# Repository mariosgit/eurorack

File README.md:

# Changes by mariosgit..

in branch mb/402to603
* Marbles 402->603
* Paits 402->603

in branch master
* Stages, fixed LED resistor 15k -> 150ohm
* Grids changed plug footprint

# Mutable Instruments' Eurorack Modules.

* [Blades](http://mutable-instruments.net/modules/blades): Dual multimode filter.
* [Blinds](http://mutable-instruments.net/modules/blinds): Quad VC-polarizer.
* [Braids](http://mutable-instruments.net/modules/braids): Macro-oscillator.
* [Branches](http://mutable-instruments.net/modules/branches): Dual Bernoulli gate.
* [Clouds](http://mutable-instruments.net/modules/clouds): Texture synthesizer.
* [Ears](http://mutable-instruments.net/modules/ears): Contact microphone.
* [Edges](http://mutable-instruments.net/modules/edges): Quad chiptune digital oscillator.
* [Elements](http://mutable-instruments.net/modules/elements): Modal synthesizer.
* [Frames](http://mutable-instruments.net/modules/frames): Keyframer/mixer.
* [Grids](http://mutable-instruments.net/modules/grids): Topographic drum sequencer.
* [Kinks](http://mutable-instruments.net/modules/kinks): Utility module - rectifier, analog logic, S&H, noise.
* [Links](http://mutable-instruments.net/modules/links): Utility module - buffer, mixer.
* [Marbles](http://mutable-instruments.net/modules/marbles): Random sampler.
* [Peaks](http://mutable-instruments.net/modules/peaks): Dual trigger converter.
* [Plaits](http://mutable-instruments.net/modules/plaits): Macro oscillator.
* [Rings](http://mutable-instruments.net/modules/rings): Resonator.
* [Ripples](http://mutable-instruments.net/modules/ripples): Liquid 2-pole BP, 2-pole LP and 4-pole LP filter.
* [Shades](http://mutable-instruments.net/modules/shades): Triple attenuverter.
* [Shelves](http://mutable-instruments.net/modules/shelves): EQ filter.
* [Stages](http://mutable-instruments.net/modules/stages): Segment generator.
* [Streams](http://mutable-instruments.net/modules/streams): Dual dynamics gate.
* [Tides](http://mutable-instruments.net/modules/tides): Tidal modulator.
* [Veils](http://mutable-instruments.net/modules/veils): Quad VCA.
* [Volts](http://mutable-instruments.net/modules/volts): +5V power module.
* [Warps](http://mutable-instruments.net/modules/warps): Meta-modulator.
* [Yarns](http://mutable-instruments.net/modules/yarns): MIDI interface.

License
=======

Code (AVR projects): GPL3.0.

Code (STM32F projects): MIT license.

Hardware: cc-by-sa-3.0

By: Emilie Gillet (emilie.o.gillet@gmail.com)

Guidelines for derivative works
===============================

**Mutable Instruments is a registered trademark.**

The name "Mutable Instruments" should not be used on any of the derivative works you create from these files.

We do not recommend you to keep the original name of the Mutable Instruments module for your derivative works.

For example, your 5U adaptation of Mutable Instruments Clouds can be called "Foobar Modular - Particle Generator".

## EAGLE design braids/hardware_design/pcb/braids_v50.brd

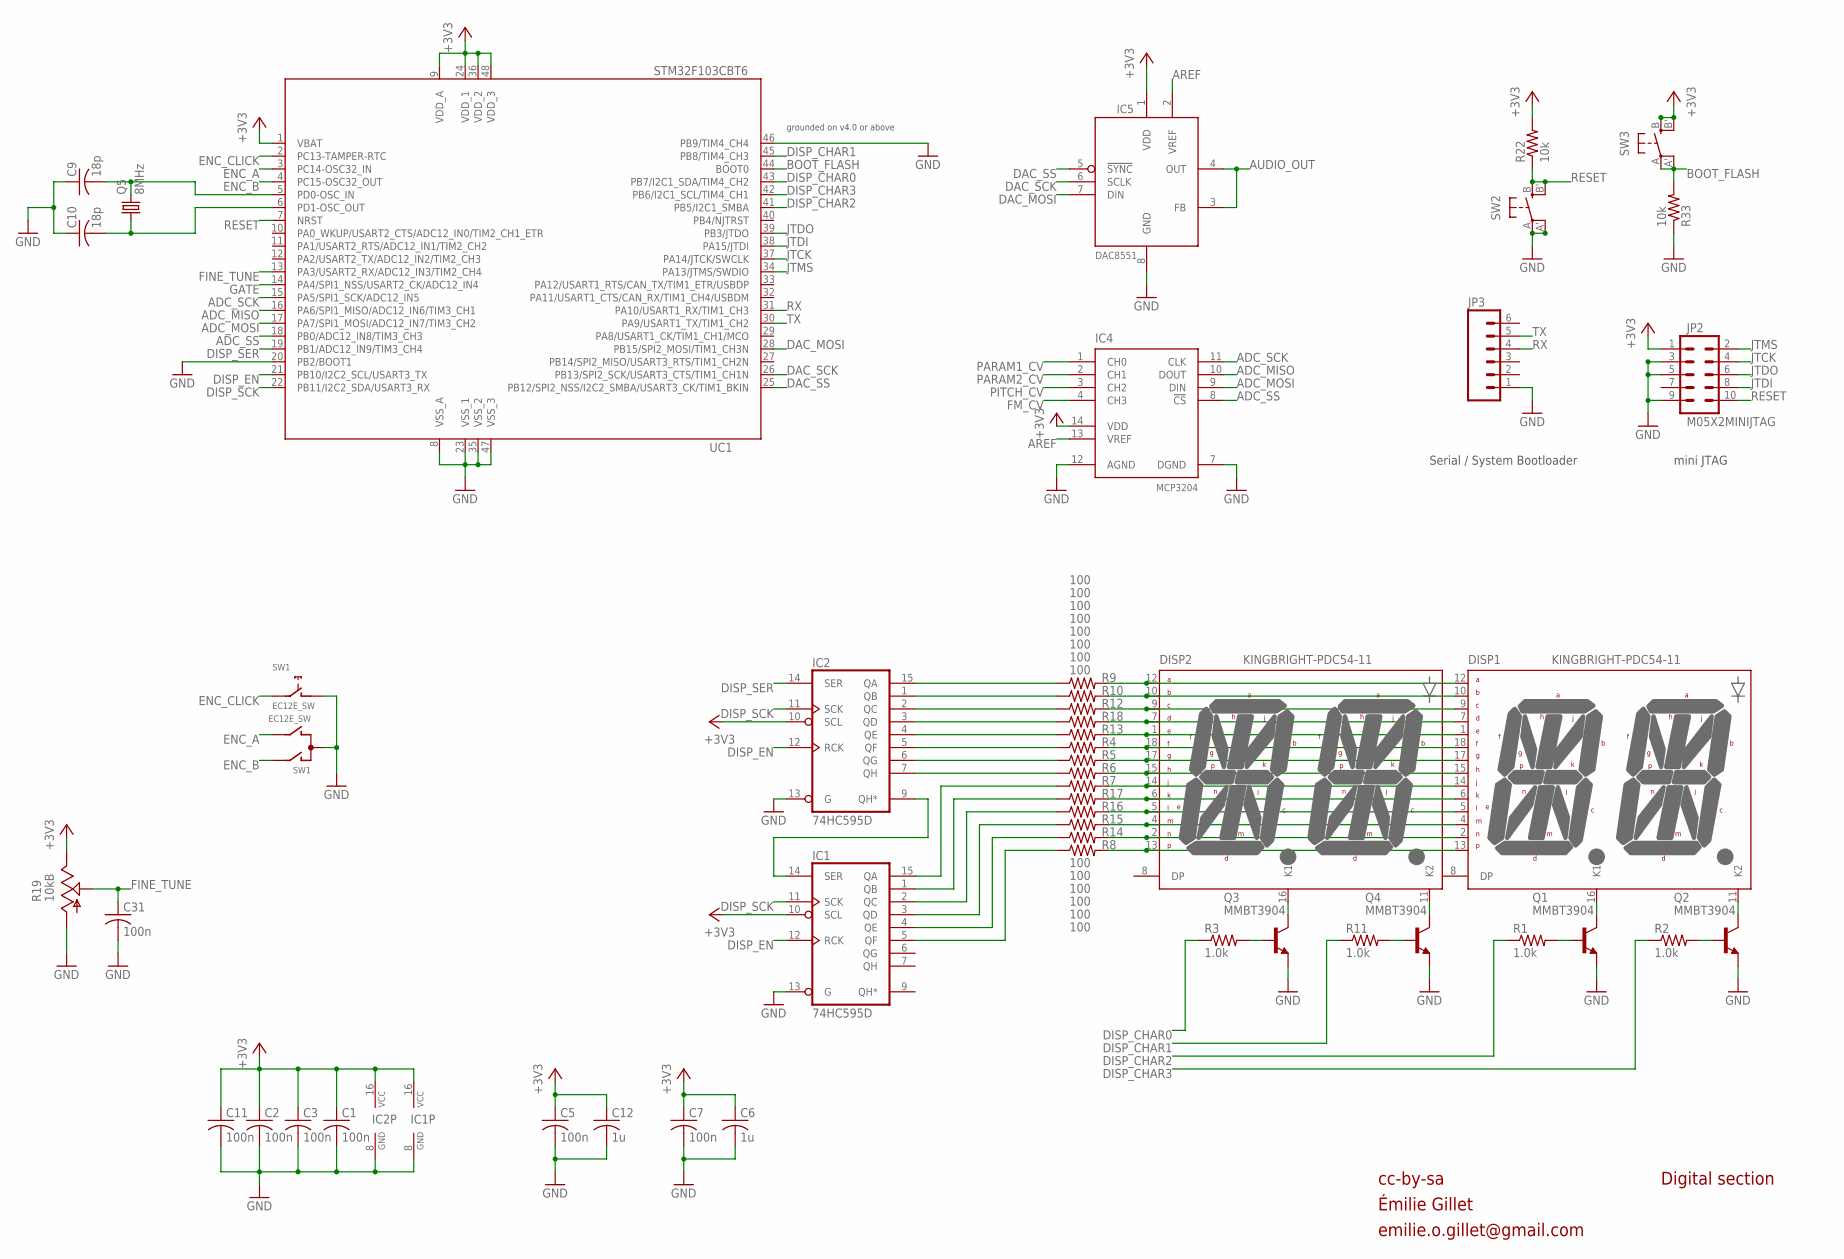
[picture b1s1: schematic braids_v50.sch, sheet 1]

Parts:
C1, C2, C3, C5, C7, C11, C31: 100n; C0603
C6, C12: 1u; C0603
C9, C10: 18p; C0603
DISP1, DISP2: KINGBRIGHT-PDC54-11; PDC54
IC1, IC2: 74HC595D; SO16
IC4: MCP3204; SO14
IC5: DAC8551; MSOP-8
JP2: M05X2MINIJTAG; 2X5-1.27
JP3: M06SIP; 1X06
Q1, Q2, Q3, Q4: MMBT3904; SOT23-BEC
Q5: 8MHz; HC49UP
R1, R2, R3, R11: 1.0k; R0603
R4, R5, R6, R7, R8, R9, R10, R12, R13, R14, R15, R16, R17, R18: 100; R0603
R19: 10kB; ALPS_POT_VERTICAL_PS
R22, R33: 10k; R0603
SW1: EC12E_SW; ALPS_EC12E_SW
SW2, SW3: EVQQ2; EVQ-Q2
UC1: STM32F103CBT6; LQFP48

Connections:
+3V3: C1.1, C2.1, C3.1, C5.1, C6.1, C7.1, C11.1, C12.1, IC1.10 (SCL), IC1.16 (VCC), IC2.10 (SCL), IC2.16 (VCC), IC4.14 (VDD), IC5.1 (VDD), JP2.1, R19.P$1 (E), R22.2, SW3.B (S), SW3.B' (S1), UC1.1 (VBAT), UC1.9 (VDD_A), UC1.24 (VDD_1), UC1.36 (VDD_2), UC1.48 (VDD_3); also elsewhere on the board
ADC_MISO: IC4.10 (DOUT), UC1.16 (PA6/SPI1_MISO/ADC12_IN6/TIM3_CH1)
ADC_MOSI: IC4.9 (DIN), UC1.17 (PA7/SPI1_MOSI/ADC12_IN7/TIM3_CH2)
ADC_SCK: IC4.11 (CLK), UC1.15 (PA5/SPI1_SCK/ADC12_IN5)
ADC_SS: IC4.8 (!CS), UC1.18 (PB0/ADC12_IN8/TIM3_CH3)
AREF: IC4.13 (VREF), IC5.2 (VREF); also elsewhere on the board
AUDIO_OUT: IC5.3 (FB), IC5.4 (OUT); also elsewhere on the board
BOOT_FLASH: R33.2, SW3.A, SW3.A' (P1), UC1.44 (BOOT0)
DAC_MOSI: IC5.7 (DIN), UC1.28 (PB15/SPI2_MOSI/TIM1_CH3N)
DAC_SCK: IC5.6 (SCLK), UC1.26 (PB13/SPI2_SCK/USART3_CTS/TIM1_CH1N)
DAC_SS: IC5.5 (!SYNC), UC1.25 (PB12/SPI2_NSS/I2C2_SMBA/USART3_CK/TIM1_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)
DISP_CHAR0: R3.1, UC1.43 (PB7/I2C1_SDA/TIM4_CH2)
DISP_CHAR1: R11.1, UC1.45 (PB8/TIM4_CH3)
DISP_CHAR2: R1.1, UC1.41 (PB5/I2C1_SMBA)
DISP_CHAR3: R2.1, UC1.42 (PB6/I2C1_SCL/TIM4_CH1)
DISP_EN: IC1.12 (RCK), IC2.12 (RCK), UC1.21 (PB10/I2C2_SCL/USART3_TX)
DISP_SCK: IC1.11 (SCK), IC2.11 (SCK), UC1.22 (PB11/I2C2_SDA/USART3_RX)
DISP_SER: IC2.14 (SER), UC1.19 (PB1/ADC12_IN9/TIM3_CH4)
ENC_A: SW1.B, UC1.3 (PC14-OSC32_IN)
ENC_B: SW1.A, UC1.4 (PC15-OSC32_OUT)
ENC_CLICK: SW1.E (2), UC1.2 (PC13-TAMPER-RTC)
FINE_TUNE: C31.1, R19.P$2 (S), UC1.13 (PA3/USART2_RX/ADC12_IN3/TIM2_CH4)
FM_CV: IC4.4 (CH3); also elsewhere on the board
GATE: UC1.14 (PA4/SPI1_NSS/USART2_CK/ADC12_IN4); also elsewhere on the board
GND: C1.2, C2.2, C3.2, C5.2, C6.2, C7.2, C9.1, C10.1, C11.2, C12.2, C31.2, IC1.8 (GND), IC1.13 (G), IC2.8 (GND), IC2.13 (G), IC4.7 (DGND), IC4.12 (AGND), IC5.8 (GND), JP2.3, JP2.5, JP2.9, JP3.1, Q1.E, Q2.E, Q3.E, Q4.E, R19.P$3 (A), R33.1, SW1.C, SW1.D (1), SW2.A, SW2.A' (P1), UC1.8 (VSS_A), UC1.20 (PB2/BOOT1), UC1.23 (VSS_1), UC1.35 (VSS_2), UC1.46 (PB9/TIM4_CH4), UC1.47 (VSS_3); also elsewhere on the board
JTCK: JP2.4, UC1.37 (PA14/JTCK/SWCLK)
JTDI: JP2.8, UC1.38 (PA15/JTDI)
JTDO: JP2.6, UC1.39 (PB3/JTDO)
JTMS: JP2.2, UC1.34 (PA13/JTMS/SWDIO)
unnamed: DISP2.16 (K1), Q3.C
unnamed: DISP2.11 (K2), Q4.C
unnamed: DISP1.16 (K1), Q1.C
unnamed: DISP1.11 (K2), Q2.C
unnamed: Q3.B, R3.2
unnamed: Q4.B, R11.2
unnamed: C9.2, Q5.2, UC1.5 (PD0-OSC_IN)
unnamed: C10.2, Q5.1, UC1.6 (PD1-OSC_OUT)
unnamed: Q1.B, R1.2
unnamed: Q2.B, R2.2
unnamed: DISP1.12 (A), DISP2.12 (A), R9.2
unnamed: DISP1.10 (B), DISP2.10 (B), R10.2
unnamed: DISP1.9 (C), DISP2.9 (C), R12.2
unnamed: DISP1.7 (D), DISP2.7 (D), R18.2
unnamed: DISP1.1 (E), DISP2.1 (E), R13.2
unnamed: DISP1.18 (F), DISP2.18 (F), R4.2
unnamed: DISP1.17 (G), DISP2.17 (G), R5.2
unnamed: DISP1.15 (H), DISP2.15 (H), R6.2
unnamed: DISP1.14 (J), DISP2.14 (J), R7.2
unnamed: DISP1.6 (K), DISP2.6 (K), R17.2
unnamed: DISP1.5 (L), DISP2.5 (L), R16.2
unnamed: DISP1.4 (M), DISP2.4 (M), R15.2
unnamed: DISP1.2 (N), DISP2.2 (N), R14.2
unnamed: DISP1.13, DISP2.13, R8.2
unnamed: IC2.7 (QH), R6.1
unnamed: IC1.14 (SER), IC2.9 (QH*)
unnamed: IC2.15 (QA), R9.1
unnamed: IC2.1 (QB), R10.1
unnamed: IC2.2 (QC), R12.1
unnamed: IC2.3 (QD), R18.1
unnamed: IC2.4 (QE), R13.1
unnamed: IC2.5 (QF), R4.1
unnamed: IC2.6 (QG), R5.1
unnamed: IC1.15 (QA), R7.1
unnamed: IC1.1 (QB), R17.1
unnamed: IC1.2 (QC), R16.1
unnamed: IC1.3 (QD), R15.1
unnamed: IC1.4 (QE), R14.1
unnamed: IC1.5 (QF), R8.1
PARAM1_CV: IC4.1 (CH0); also elsewhere on the board
PARAM2_CV: IC4.2 (CH1); also elsewhere on the board
PITCH_CV: IC4.3 (CH2); also elsewhere on the board
RESET: JP2.10, R22.1, SW2.B (S), SW2.B' (S1), UC1.7 (NRST)
RX: JP3.4, UC1.31 (PA10/USART1_RX/TIM1_CH3)
TX: JP3.5, UC1.30 (PA9/USART1_TX/TIM1_CH2)

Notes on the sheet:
cc-by-sa
Serial / System Bootloader
mini JTAG
Digital section
grounded on v4.0 or above
Émilie Gillet
emilie.o.gillet@gmail.com

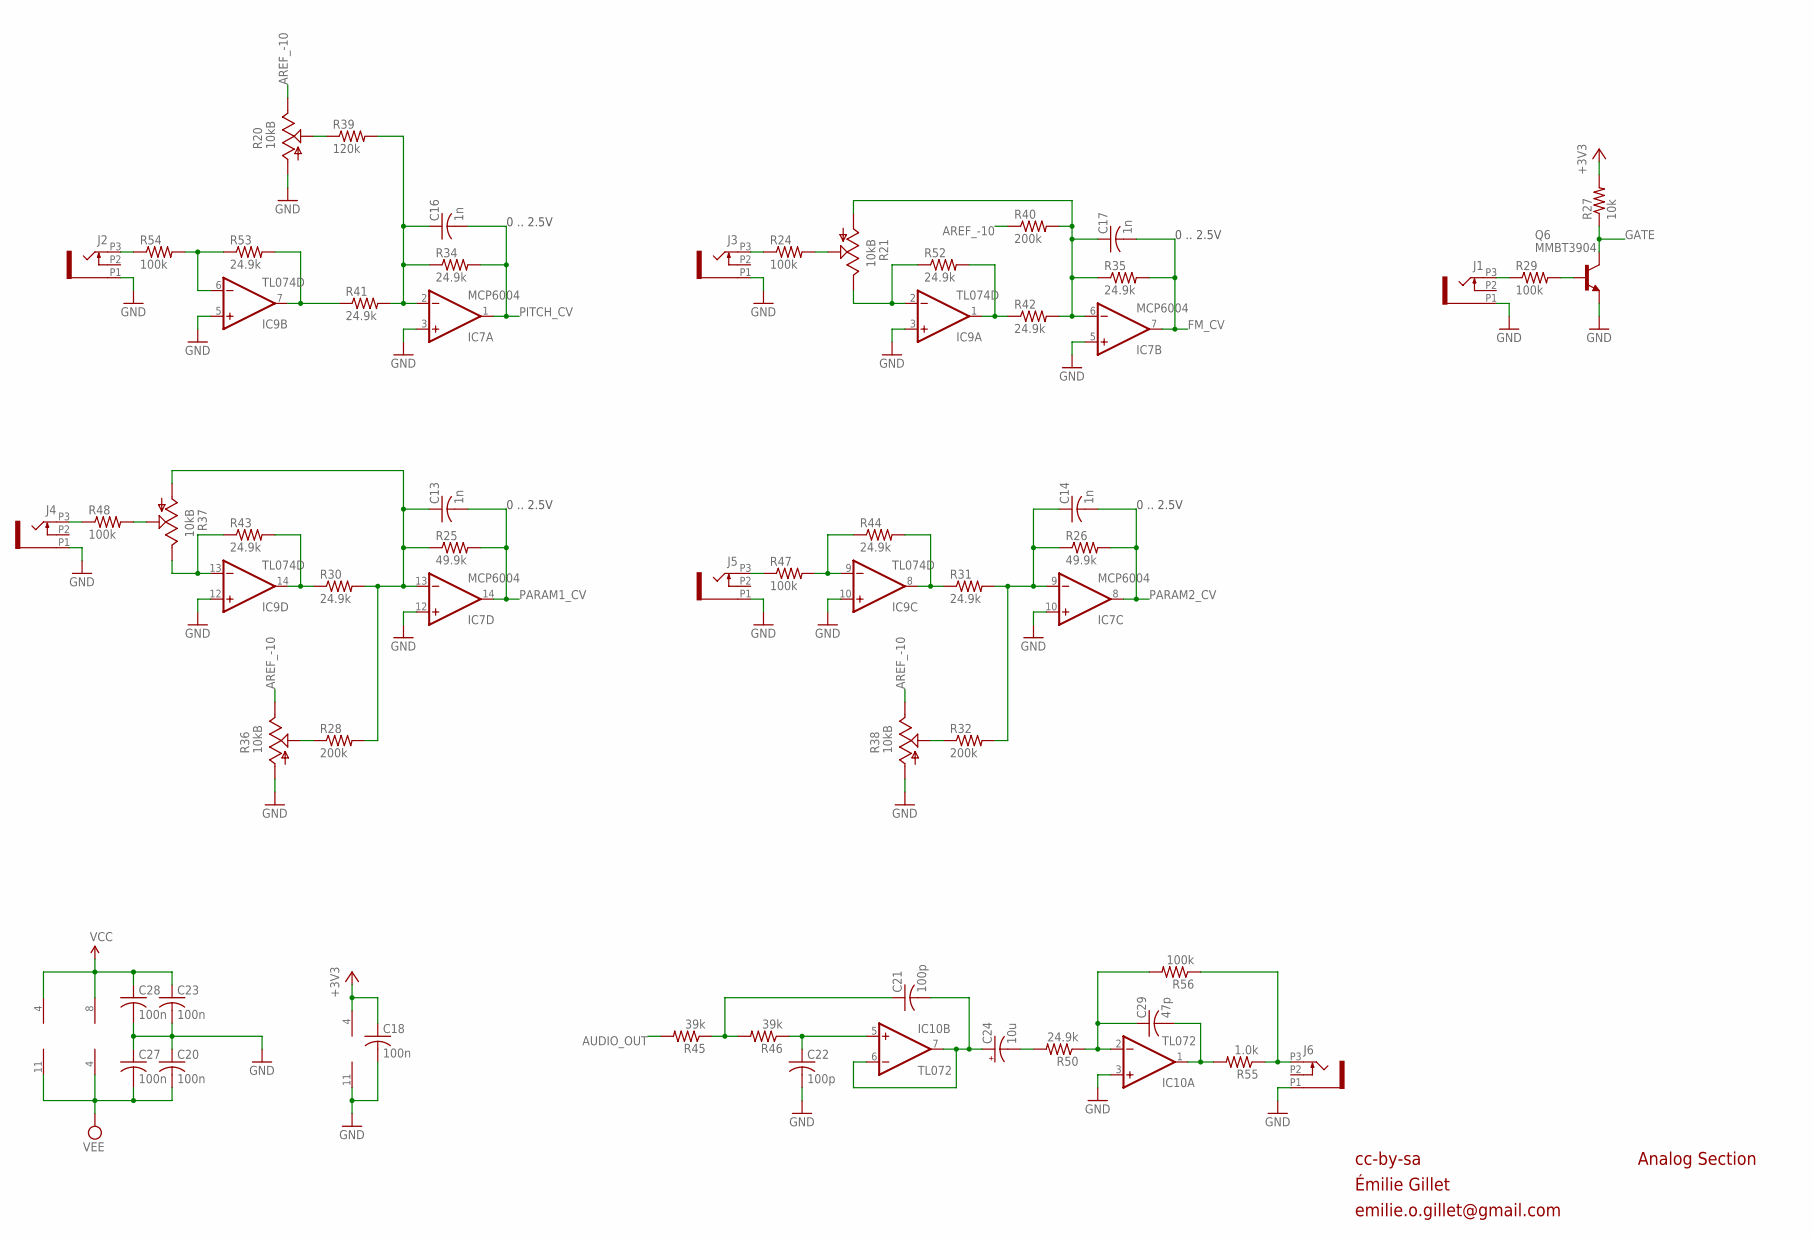
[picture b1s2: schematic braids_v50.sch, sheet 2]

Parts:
C13, C14, C16, C17: 1n; C0603
C18, C20, C23, C27, C28: 100n; C0603
C21, C22: 100p; C0603
C24: 10u; PANASONIC_B
C29: 47p; C0603
IC7: MCP6004; SO14
IC9: TL074D; SO14
IC10: TL072; SO08
J1, J2, J3, J4, J5, J6: PJ301_THONKICONN6; WQP_PJ_301M6
Q6: MMBT3904; SOT23-BEC
R20, R21, R36, R37, R38: 10kB; ALPS_POT_VERTICAL_PS
R24, R29, R47, R48, R54, R56: 100k; R0603
R25, R26: 49.9k; R0603
R27: 10k; R0603
R28, R32, R40: 200k; R0603
R30, R31, R34, R35, R41, R42, R43, R44, R50, R52, R53: 24.9k; R0603
R39: 120k; R0603
R45, R46: 39k; R0603
R55: 1.0k; R0603

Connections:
+3V3: C18.1, IC7.4 (V+), R27.2; also elsewhere on the board
AREF_-10: R20.P$1 (E), R36.P$1 (E), R38.P$1 (E), R40.1; also elsewhere on the board
AUDIO_OUT: R45.2; also elsewhere on the board
FM_CV: C17.2, IC7.7 (OUT), R35.2; also elsewhere on the board
GATE: Q6.C, R27.1; also elsewhere on the board
GND: C18.2, C20.1, C22.2, C23.2, C27.1, C28.2, IC7.3 (+IN), IC7.5 (+IN), IC7.10 (+IN), IC7.11 (V-), IC7.12 (+IN), IC9.3 (+IN), IC9.5 (+IN), IC9.10 (+IN), IC9.12 (+IN), IC10.3 (+IN), J1.P1 (1), J2.P1 (1), J3.P1 (1), J4.P1 (1), J5.P1 (1), J6.P1 (1), Q6.E, R20.P$3 (A), R36.P$3 (A), R38.P$3 (A); also elsewhere on the board
unnamed: IC9.7 (OUT), R41.1, R53.2
unnamed: R20.P$2 (S), R39.1
unnamed: J2.P3 (3), R54.1
unnamed: C16.1, IC7.2 (-IN), R34.1, R39.2, R41.2
unnamed: IC9.6 (-IN), R53.1, R54.2
unnamed: J3.P3 (3), R24.1
unnamed: J4.P3 (3), R48.1
unnamed: R21.P$2 (S), R24.2
unnamed: IC9.13 (-IN), R37.P$1 (E), R43.1
unnamed: IC9.14 (OUT), R30.1, R43.2
unnamed: IC9.2 (-IN), R21.P$1 (E), R52.1
unnamed: IC9.1 (OUT), R42.1, R52.2
unnamed: C17.1, IC7.6 (-IN), R21.P$3 (A), R35.1, R40.2, R42.2
unnamed: J1.P3 (3), R29.1
unnamed: IC9.8 (OUT), R31.1, R44.2
unnamed: C13.1, IC7.13 (-IN), R25.1, R28.2, R30.2, R37.P$3 (A)
unnamed: J5.P3 (3), R47.1
unnamed: R28.1, R36.P$2 (S)
unnamed: R37.P$2 (S), R48.2
unnamed: IC9.9 (-IN), R44.1, R47.2
unnamed: R32.1, R38.P$2 (S)
unnamed: Q6.B, R29.2
unnamed: C21.2, C24.+, IC10.6 (-IN), IC10.7 (OUT)
unnamed: C24.-, R50.2
unnamed: C22.1, IC10.5 (+IN), R46.1
unnamed: C14.1, IC7.9 (-IN), R26.1, R31.2, R32.2
unnamed: C21.1, R45.1, R46.2
unnamed: J6.P3 (3), R55.1, R56.1
unnamed: C29.2, IC10.1 (OUT), R55.2
unnamed: C29.1, IC10.2 (-IN), R50.1, R56.2
PARAM1_CV: C13.2, IC7.14 (OUT), R25.2; also elsewhere on the board
PARAM2_CV: C14.2, IC7.8 (OUT), R26.2; also elsewhere on the board
PITCH_CV: C16.2, IC7.1 (OUT), R34.2; also elsewhere on the board
VCC: C23.1, C28.1, IC9.4 (V+), IC10.8 (V+); also elsewhere on the board
VEE: C20.2, C27.2, IC9.11 (V-), IC10.4 (V-); also elsewhere on the board

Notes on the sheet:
cc-by-sa
Analog Section
0 .. 2.5V
Émilie Gillet
emilie.o.gillet@gmail.com

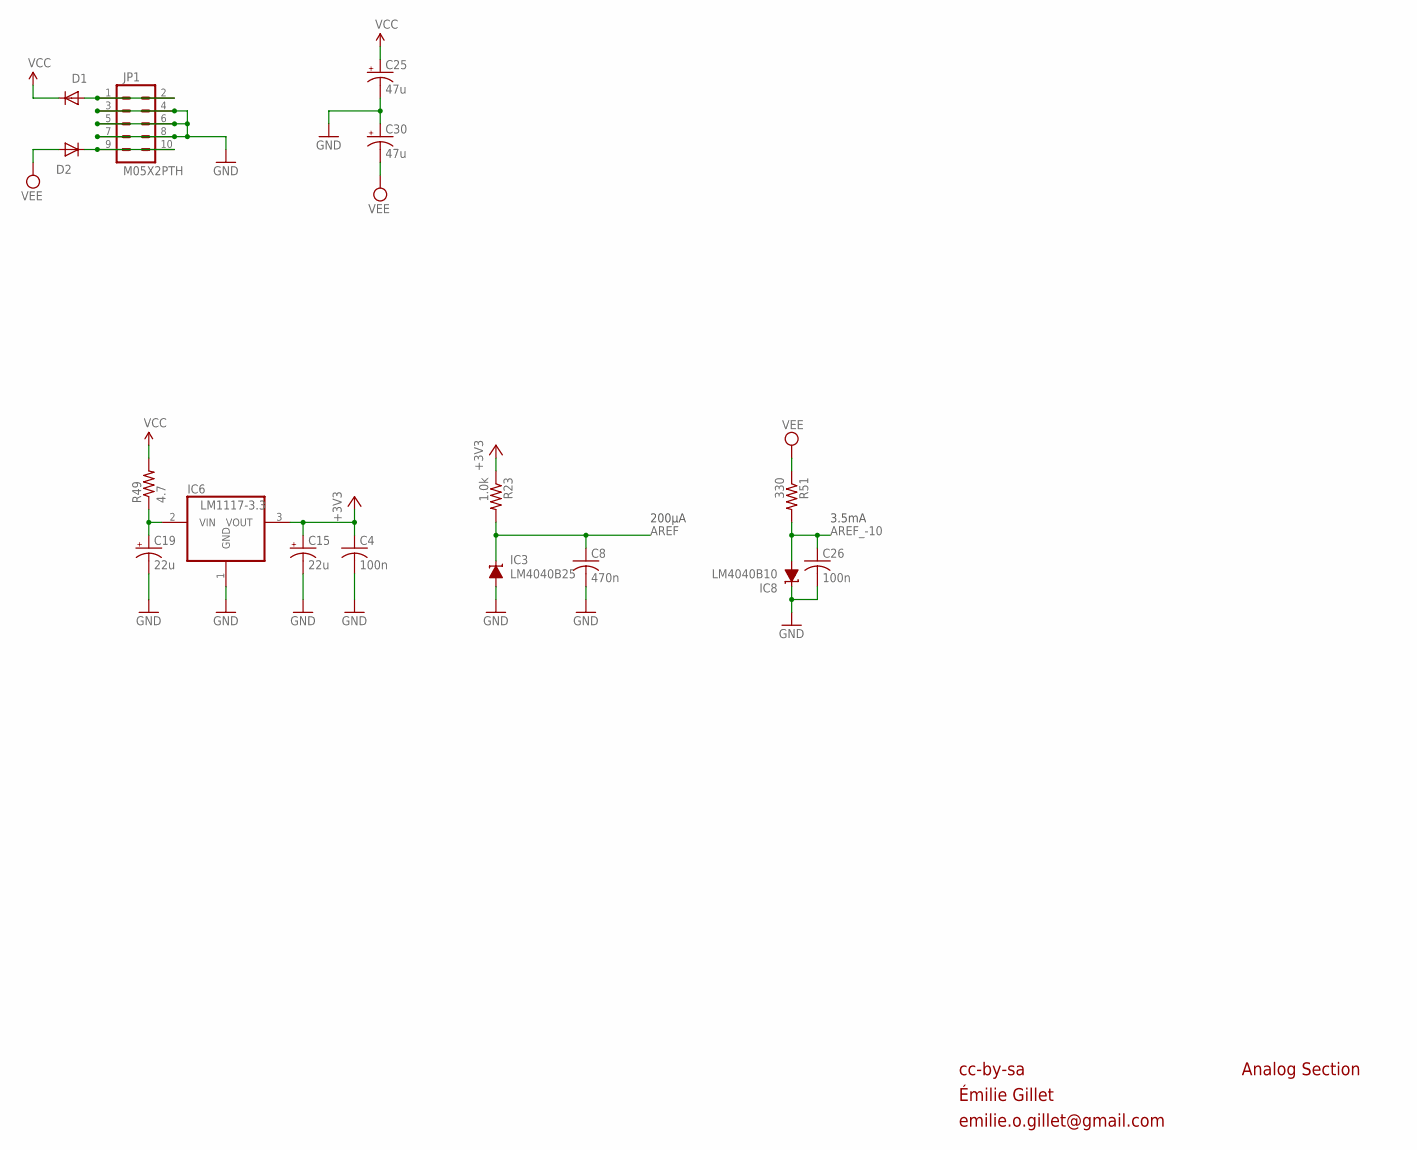
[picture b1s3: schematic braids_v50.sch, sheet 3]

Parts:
C4, C26: 100n; C0603
C8: 470n; C0603
C15, C19: 22u; PANASONIC_C
C25, C30: 47u; PANASONIC_D
D1, D2: 1N5819HW; SOD123
IC3: LM4040B25; DBZ_R-PDSO-G3
IC6: LM1117-3.3; TO252
IC8: LM4040B10; DBZ_R-PDSO-G3
JP1: M05X2PTH; AVR_ICSP
R23: 1.0k; R0603
R49: 4.7; R1206
R51: 330; R0603

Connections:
+3V3: C4.1, C15.+, IC6.3 (VOUT), R23.1; also elsewhere on the board
AREF: C8.1, IC3.1 (C), R23.2; also elsewhere on the board
AREF_-10: C26.1, IC8.2 (A), R51.2; also elsewhere on the board
GND: C4.2, C8.2, C15.-, C19.-, C25.-, C26.2, C30.+, IC3.2 (A), IC6.1 (GND), IC8.1 (C), JP1.3, JP1.4, JP1.5, JP1.6, JP1.7, JP1.8; also elsewhere on the board
unnamed: C19.+, IC6.2 (VIN), R49.1
unnamed: D1.A, JP1.1, JP1.2
unnamed: D2.C, JP1.9, JP1.10
VCC: C25.+, D1.C, R49.2; also elsewhere on the board
VEE: C30.-, D2.A, R51.1; also elsewhere on the board

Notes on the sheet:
3.5mA
200µA
cc-by-sa
Analog Section
Émilie Gillet
emilie.o.gillet@gmail.com

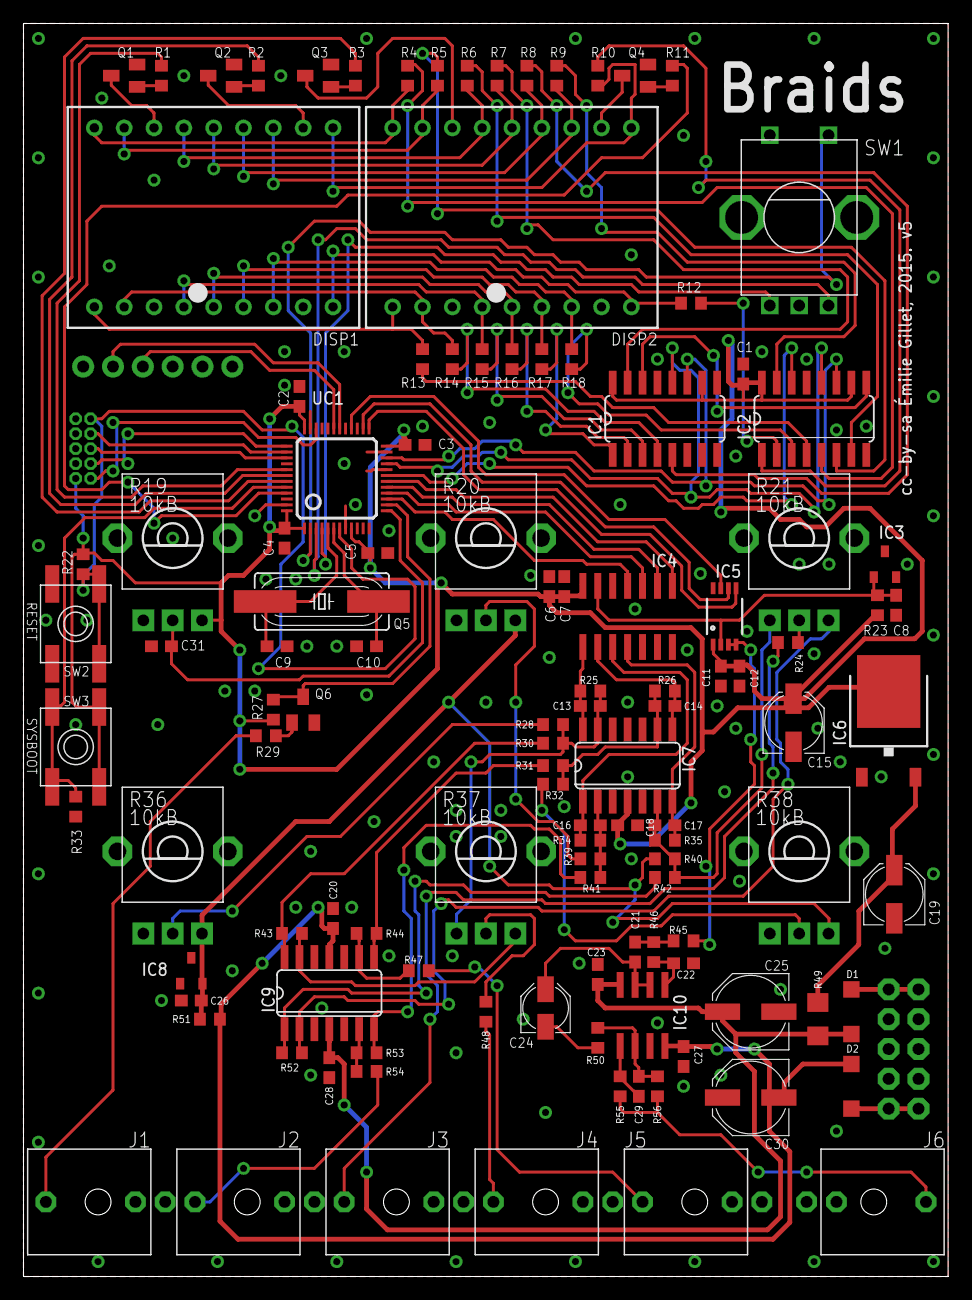
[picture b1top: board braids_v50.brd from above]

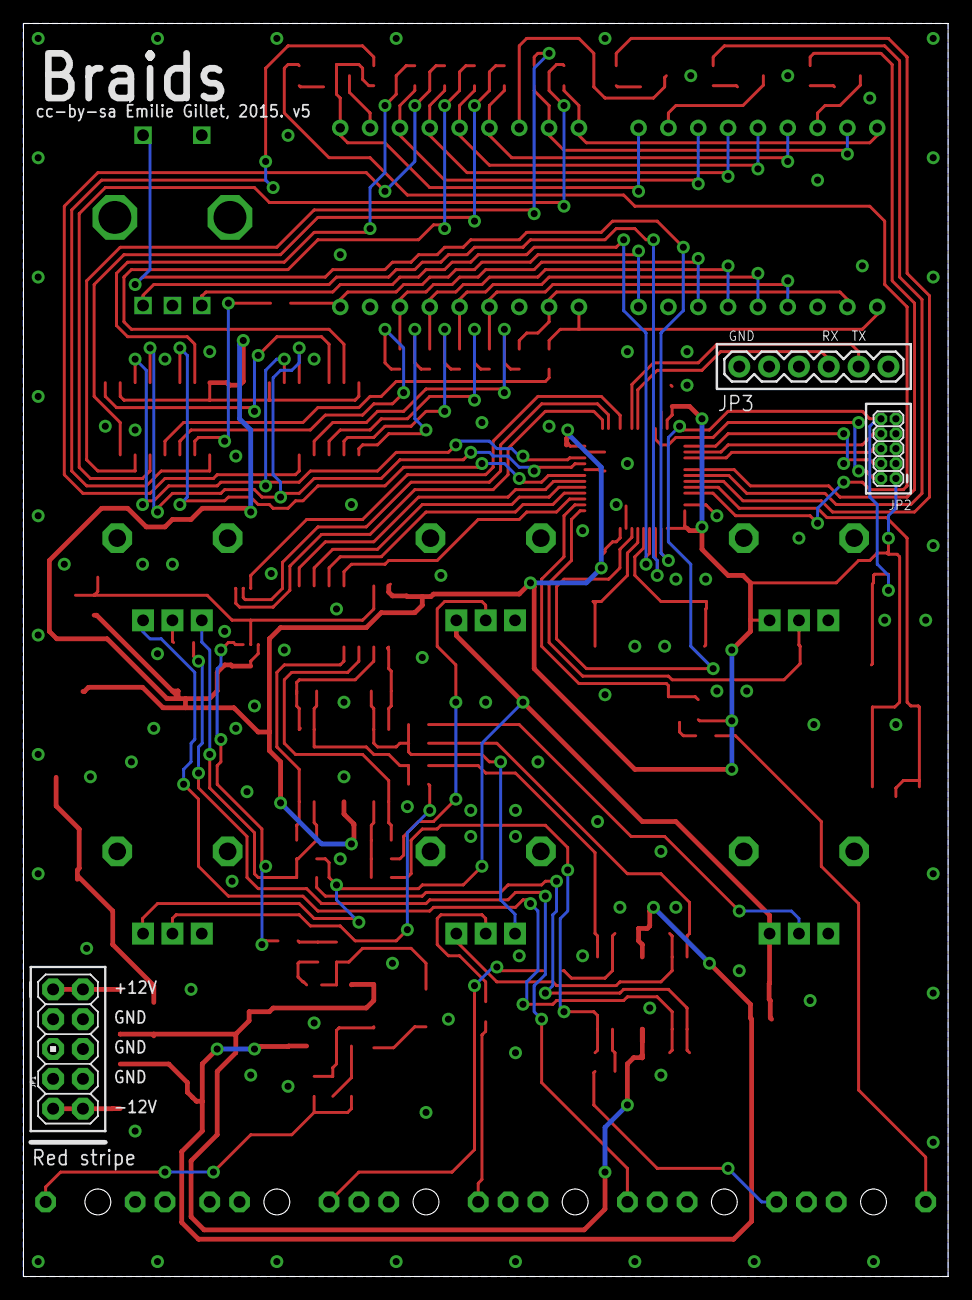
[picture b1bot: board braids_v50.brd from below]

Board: 2 copper layers, 78.7 x 106.7 mm, 120 parts (3 on the bottom side), 110 nets.

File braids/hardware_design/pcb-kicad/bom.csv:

"Reference","Value","Datasheet","Footprint","Qty","DNP"
"C1,C2,C3,C4,C5,C7,C11,C18,C20,C23,C26,C27,C28,C31","100n","","braids_v50:C0603","14",""
"C6,C12","1u","","braids_v50:C0603","2",""
"C8","470n","","braids_v50:C0603","1",""
"C9,C10","18p","","braids_v50:C0603","2",""
"C13,C14,C16,C17","1n","","braids_v50:C0603","4",""
"C15,C19","22u","","braids_v50:PANASONIC_C","2",""
"C21,C22","100p","","braids_v50:C0603","2",""
"C24","10u","","braids_v50:PANASONIC_B","1",""
"C25,C30","47u","","braids_v50:PANASONIC_D","2",""
"C29","47p","","braids_v50:C0603","1",""
"D1,D2","1N5819HW","~","Diode_SMD:Nexperia_CFP3_SOD-123W","2",""
"DISP1,DISP2","KINGBRIGHT-PDC54-11","","braids_v50:PDC54","2",""
"FB1","FerriteBead_Small","~","","1",""
"IC1,IC2","74595D","","braids_v50:SO16","2",""
"IC3","LM4040B25","","braids_v50:DBZ_R-PDSO-G3","1",""
"IC4","MCP3204","","braids_v50:SO14","1",""
"IC5","DAC8551","","braids_v50:MSOP-8","1",""
"IC6","LM1117-3.3","","braids_v50:TO252","1",""
"IC7","MCP6004","","braids_v50:SO14","1",""
"IC8","LM4040B10","","braids_v50:DBZ_R-PDSO-G3","1",""
"IC9","TL074D","","braids_v50:SO14","1",""
"IC10","TL072","","braids_v50:SO08","1",""
"J1,J2,J3,J4,J5,J6","PJ301_THONKICONN6","","braids_v50:WQP_PJ_301M6","6",""
"JP1","M05X2PTH","","braids_v50:AVR_ICSP","1",""
"JP2","M05X2MINIJTAG","","braids_v50:2X5-1.27","1",""
"JP3","M06SIP","","braids_v50:1X06","1",""
"Q1,Q2,Q3,Q4,Q6","MMBT3904","","braids_v50:SOT23-BEC","5",""
"Q5","8MHz","","braids_v50:HC49UP","1",""
"R1,R2,R3,R11,R23,R55","1.0k","","braids_v50:R0603","6",""
"R4,R5,R6,R7,R8,R9,R10,R12,R13,R14,R15,R16,R17,R18","100","","braids_v50:R0603","14",""
"R19,R20,R21,R36,R37,R38","10kB","","braids_v50:ALPS_POT_VERTICAL_PS","6",""
"R22,R27,R33","10k","","braids_v50:R0603","3",""
"R24,R29,R47,R48,R54,R56","100k","","braids_v50:R0603","6",""
"R25,R26","49.9k","","braids_v50:R0603","2",""
"R28,R32,R40","200k","","braids_v50:R0603","3",""
"R30,R31,R34,R35,R41,R42,R43,R44,R50,R52,R53","24.9k","","braids_v50:R0603","11",""
"R39","120k","","braids_v50:R0603","1",""
"R45,R46","39k","","braids_v50:R0603","2",""
"R49","4.7","","braids_v50:R1206","1",""
"R51","330","","braids_v50:R0603","1",""
"SW1","EC12E_SW","","braids_v50:ALPS_EC12E_SW","1",""
"SW2,SW3","EVQQ2","","braids_v50:EVQ-Q2","2",""
"U1","TSR_1-2450","http://www.tracopower.com/products/tsr1.pdf","Converter_DCDC:Converter_DCDC_TRACO_TSR-1_THT","1",""
"UC1","STM32F103CBT6","","braids_v50:LQFP48","1",""

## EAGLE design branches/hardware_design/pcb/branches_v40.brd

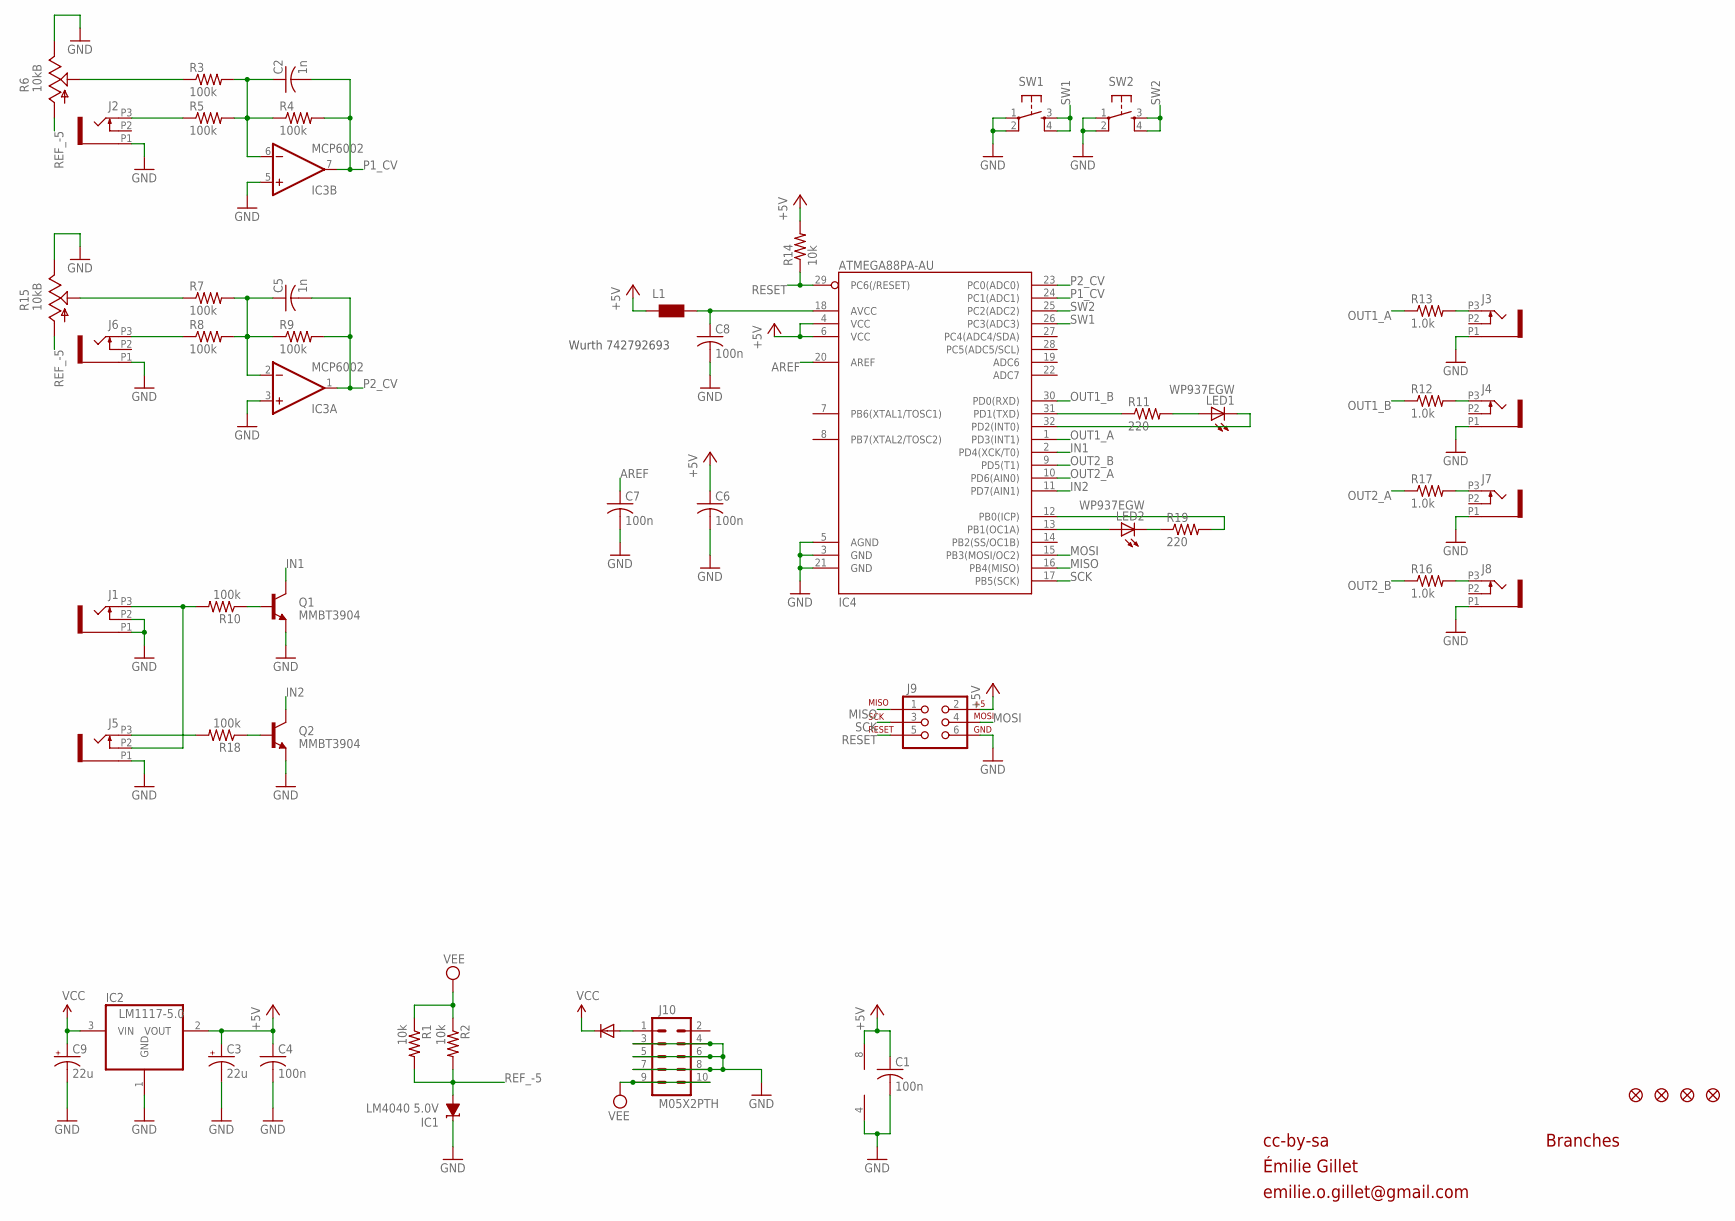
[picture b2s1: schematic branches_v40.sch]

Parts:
C1, C4, C6, C7, C8: 100n; C0603
C2, C5: 1n; C0603
C3, C9: 22u; PANASONIC_C
D1: 1N5819HW; SOD123
F1, F2, F3, F4: FIDUCIAL1X2; FIDUCIAL-1X2
IC1: LM4040 5.0V; DBZ_R-PDSO-G3
IC2: LM1117-5.0; SOT223
IC3: MCP6002; SO08
IC4: ATMEGA88PA-AU; TQFP32-08
J1, J2, J3, J4, J5, J6, J7, J8: PJ301_THONKICONN6; WQP_PJ_301M6
J9: AVR_SPI_PRG_6PTH; 2X3
J10: M05X2PTH; AVR_ICSP
L1: WE-CBF_0603; 0603
LED1, LED2: WP937EGW; LED3MM
Q1, Q2: MMBT3904; SOT23-BEC
R1, R2, R14: 10k; R0603
R3, R4, R5, R7, R8, R9, R10, R18: 100k; R0603
R6, R15: 10kB; ALPS_POT_VERTICAL_PS
R11, R19: 220; R0603
R12, R13, R16, R17: 1.0k; R0603
SW1, SW2: TAC_SWITCHPTH; TACTILE-PTH

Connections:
+5V: C1.1, C3.+, C4.1, C6.1, IC2.2 (VOUT), IC3.8 (V+), IC4.4 (VCC), IC4.6 (VCC), J9.2, L1.1, R14.2
AREF: C7.1, IC4.20 (AREF)
GATE1_IN: J1.P3 (3), J5.P2 (2), R10.2
GATE2_IN: J5.P3 (3), R18.2
GND: C1.2, C3.-, C4.2, C6.2, C7.2, C8.2, C9.-, IC1.1 (C), IC2.1 (GND), IC3.3 (+IN), IC3.4 (V-), IC3.5 (+IN), IC4.3 (GND), IC4.5 (AGND), IC4.21 (GND), J1.P1 (1), J1.P2 (2), J2.P1 (1), J3.P1 (1), J4.P1 (1), J5.P1 (1), J6.P1 (1), J7.P1 (1), J8.P1 (1), J9.6, J10.3, J10.4, J10.5, J10.6, J10.7, J10.8, Q1.E, Q2.E, R6.P$1 (E), R15.P$1 (E), SW1.1, SW1.2, SW2.1, SW2.2
IN1: IC4.2 (PD4(XCK/T0)), Q1.C
IN2: IC4.11 (PD7(AIN1)), Q2.C
MISO: IC4.16 (PB4(MISO)), J9.1
MOSI: IC4.15 (PB3(MOSI/OC2)), J9.4
unnamed: Q1.B, R10.1
unnamed: Q2.B, R18.1
unnamed: D1.A, J10.1
unnamed: C5.1, IC3.2 (-IN), R7.2, R8.2, R9.1
unnamed: J8.P3 (3), R16.2
unnamed: R7.1, R15.P$2 (S)
unnamed: R3.1, R6.P$2 (S)
unnamed: J2.P3 (3), R5.1
unnamed: J6.P3 (3), R8.1
unnamed: IC4.31 (PD1(TXD)), R11.1
unnamed: LED1.A, R11.2
unnamed: IC4.32 (PD2(INT0)), LED1.K (C)
unnamed: IC4.13 (PB1(OC1A)), LED2.A
unnamed: LED2.K (C), R19.1
unnamed: IC4.12 (PB0(ICP)), R19.2
unnamed: C2.1, IC3.6 (-IN), R3.2, R4.1, R5.2
unnamed: J3.P3 (3), R13.2
unnamed: J4.P3 (3), R12.2
unnamed: J7.P3 (3), R17.2
unnamed: C8.1, IC4.18 (AVCC), L1.2
OUT1_A: IC4.1 (PD3(INT1)), R13.1
OUT1_B: IC4.30 (PD0(RXD)), R12.1
OUT2_A: IC4.10 (PD6(AIN0)), R17.1
OUT2_B: IC4.9 (PD5(T1)), R16.1
P1_CV: C2.2, IC3.7 (OUT), IC4.24 (PC1(ADC1)), R4.2
P2_CV: C5.2, IC3.1 (OUT), IC4.23 (PC0(ADC0)), R9.2
REF_-5: IC1.2 (A), R1.2, R2.2, R6.P$3 (A), R15.P$3 (A)
RESET: IC4.29 (PC6(/RESET)), J9.5, R14.1
SCK: IC4.17 (PB5(SCK)), J9.3
SW1: IC4.26 (PC3(ADC3)), SW1.3, SW1.4
SW2: IC4.25 (PC2(ADC2)), SW2.3, SW2.4
VCC: C9.+, D1.C, IC2.3 (VIN)
VEE: J10.9, J10.10, R1.1, R2.1

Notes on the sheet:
cc-by-sa
Branches
Wurth 742792693
Émilie Gillet
emilie.o.gillet@gmail.com

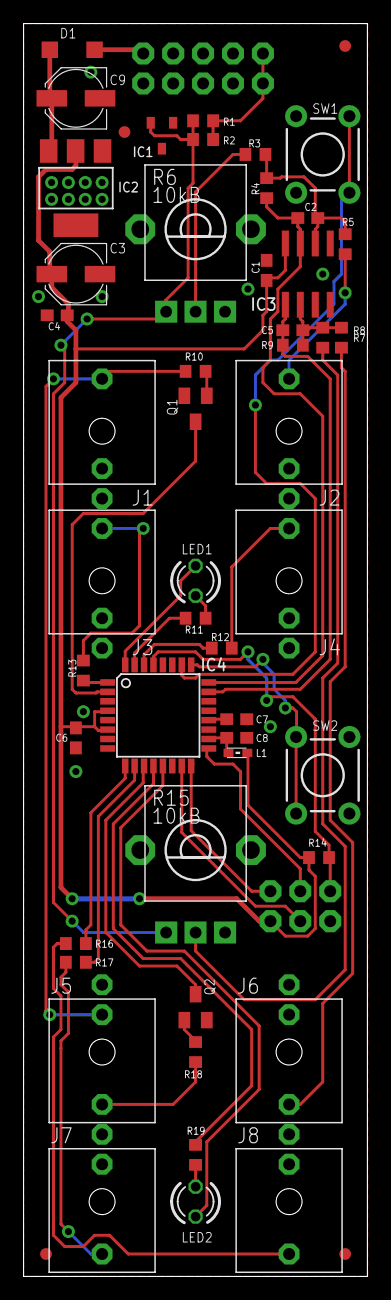
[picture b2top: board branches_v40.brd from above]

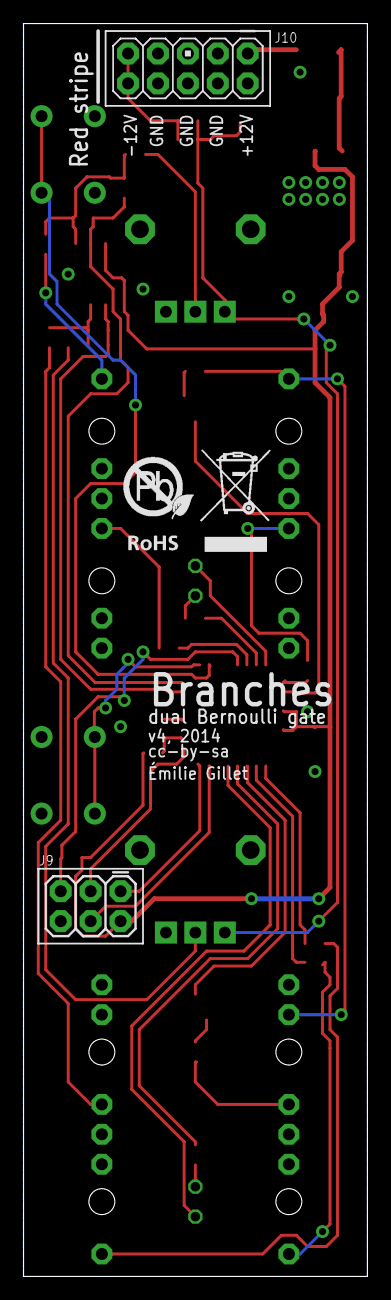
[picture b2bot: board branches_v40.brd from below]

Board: 2 copper layers, 29.2 x 106.4 mm, 55 parts (3 on the bottom side), 42 nets.

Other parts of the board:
U$1: ROHS

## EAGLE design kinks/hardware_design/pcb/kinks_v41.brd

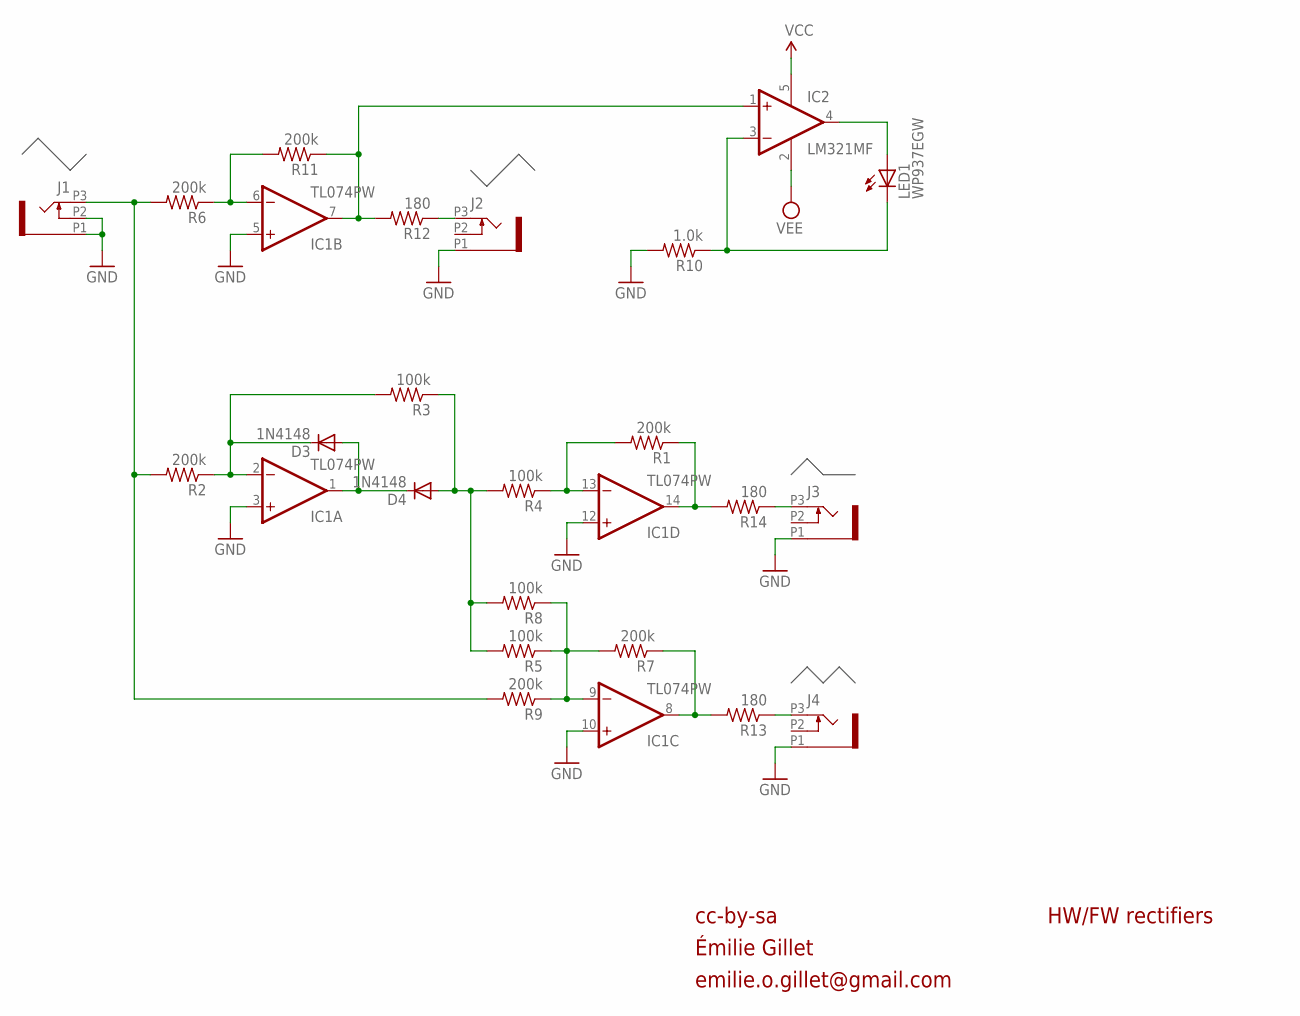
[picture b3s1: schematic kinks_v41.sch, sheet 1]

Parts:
D3, D4: 1N4148; SOD523
IC1: TL074PW; TSSOP14
IC2: LM321MF; SOT23-5
J1, J2, J3, J4: PJ301_THONKICONN6; WQP_PJ_301M6
LED1: WP937EGW; LED3MM
R1, R2, R6, R7, R9, R11: 200k; R0402
R3, R4, R5, R8: 100k; R0402
R10: 1.0k; R0402
R12, R13, R14: 180; R0402

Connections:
GND: IC1.3 (+IN), IC1.5 (+IN), IC1.10 (+IN), IC1.12 (+IN), J1.P1 (1), J1.P2 (2), J2.P1 (1), J3.P1 (1), J4.P1 (1), R10.2; also elsewhere on the board
unnamed: IC2.3 (-IN), LED1.K (C), R10.1
unnamed: IC2.4 (OUT), LED1.A
unnamed: IC1.6 (-IN), R6.1, R11.2
unnamed: IC1.7 (OUT), IC2.1 (+IN), R11.1, R12.2
unnamed: J2.P3 (3), R12.1
unnamed: D3.C, IC1.2 (-IN), R2.1, R3.2
unnamed: D3.A, D4.C, IC1.1 (OUT)
unnamed: IC1.14 (OUT), R1.1, R14.2
unnamed: IC1.13 (-IN), R1.2, R4.1
unnamed: J3.P3 (3), R14.1
unnamed: IC1.9 (-IN), R5.1, R7.2, R8.1, R9.1
unnamed: J4.P3 (3), R13.1
unnamed: IC1.8 (OUT), R7.1, R13.2
unnamed: J1.P3 (3), R2.2, R6.2, R9.2
unnamed: D4.A, R3.1, R4.2, R5.2, R8.2
VCC: IC2.5 (V+); also elsewhere on the board
VEE: IC2.2 (V-); also elsewhere on the board

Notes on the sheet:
cc-by-sa
HW/FW rectifiers
Émilie Gillet
emilie.o.gillet@gmail.com
